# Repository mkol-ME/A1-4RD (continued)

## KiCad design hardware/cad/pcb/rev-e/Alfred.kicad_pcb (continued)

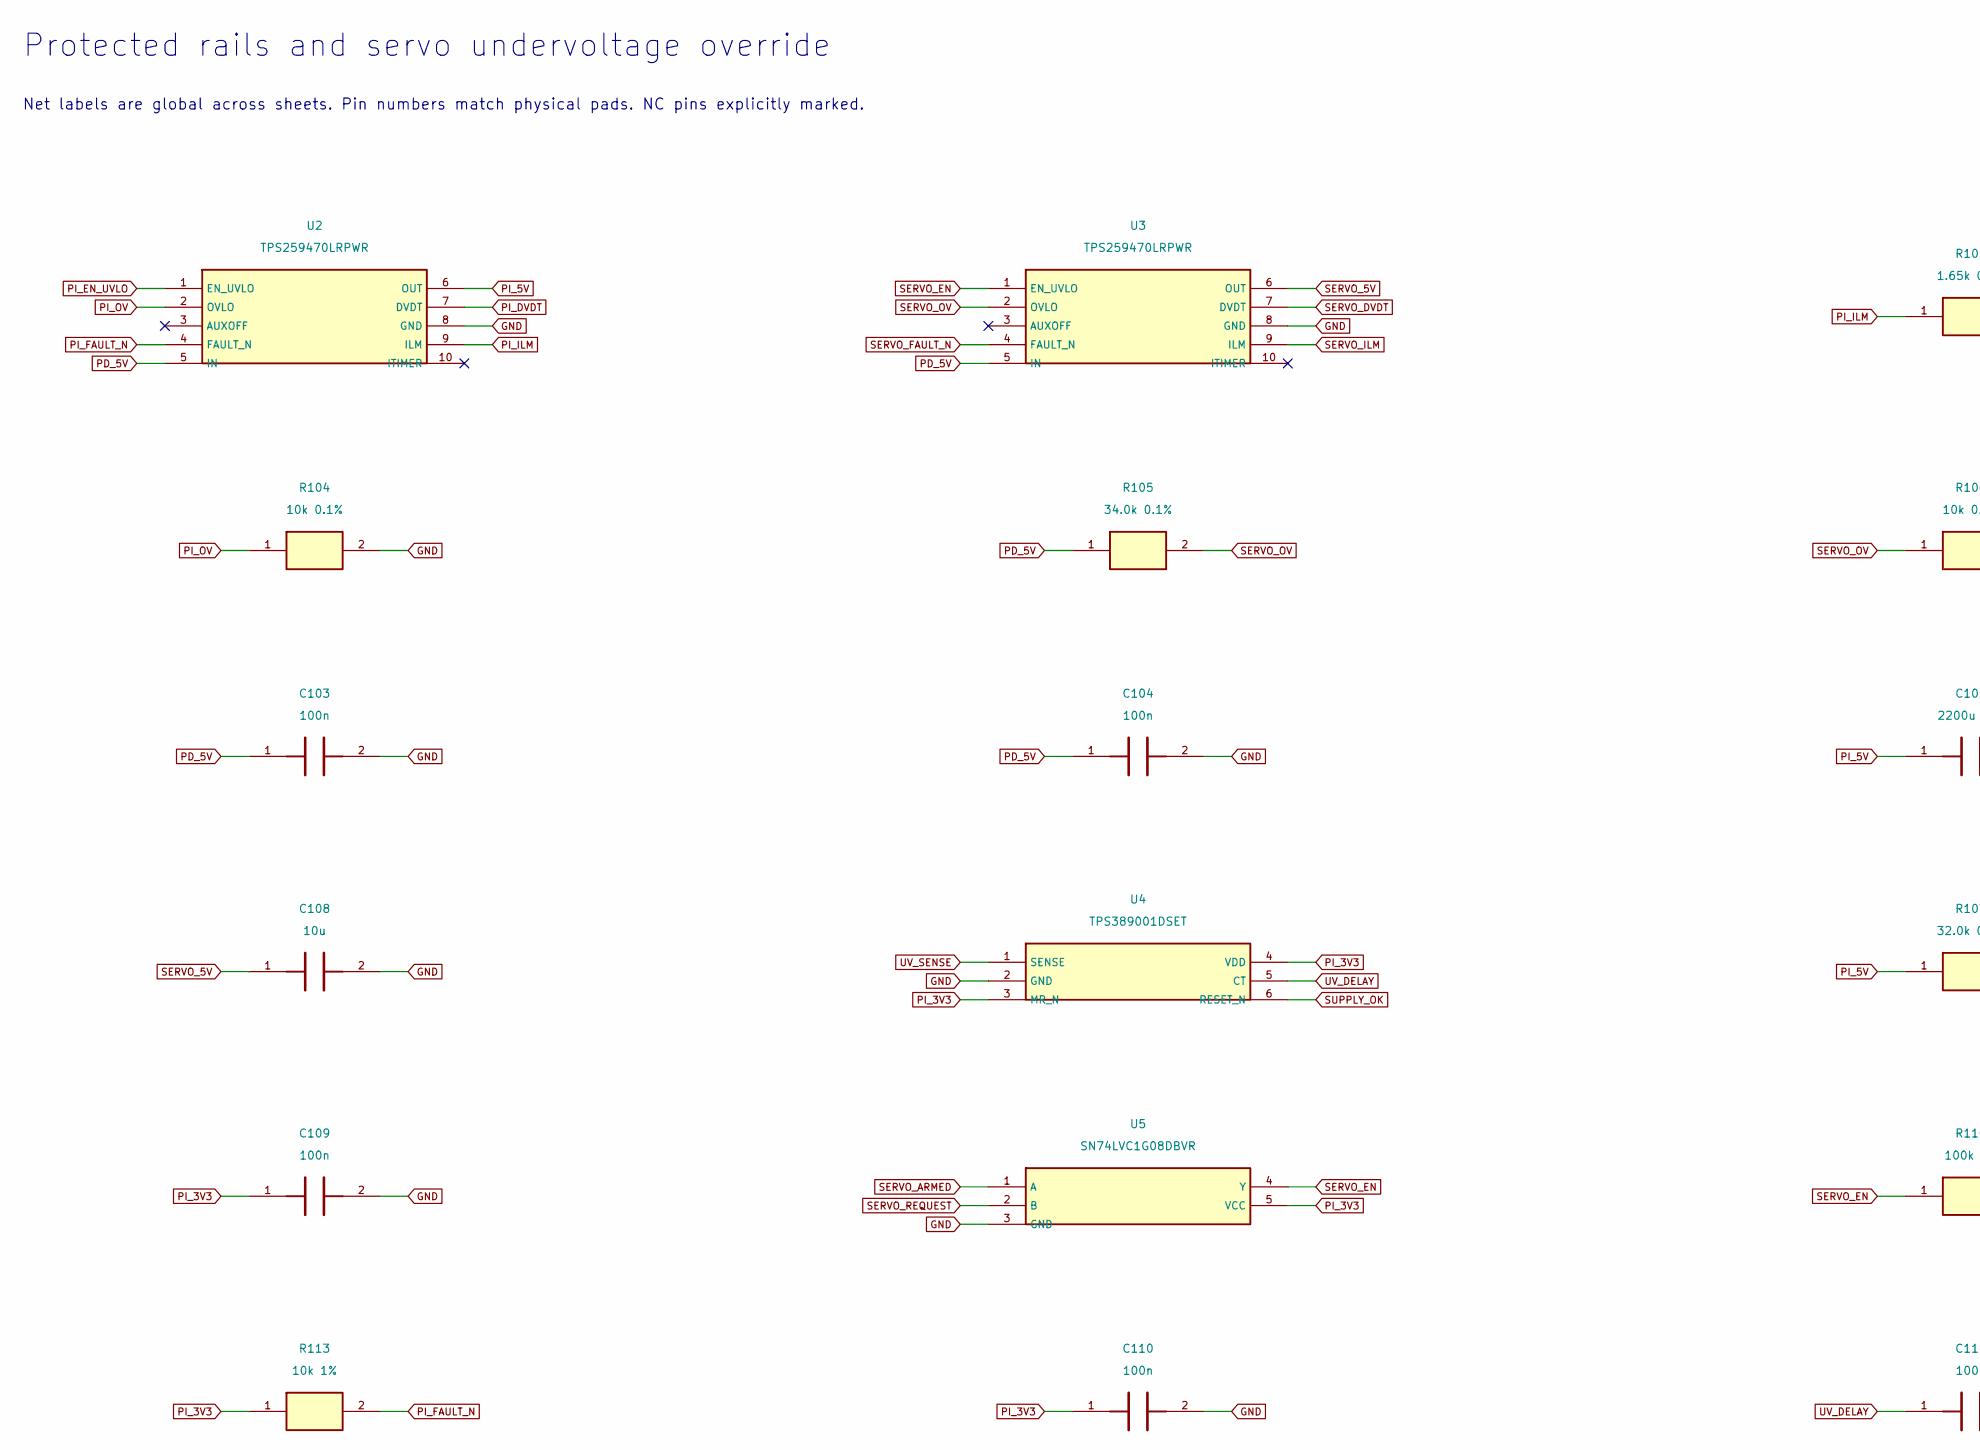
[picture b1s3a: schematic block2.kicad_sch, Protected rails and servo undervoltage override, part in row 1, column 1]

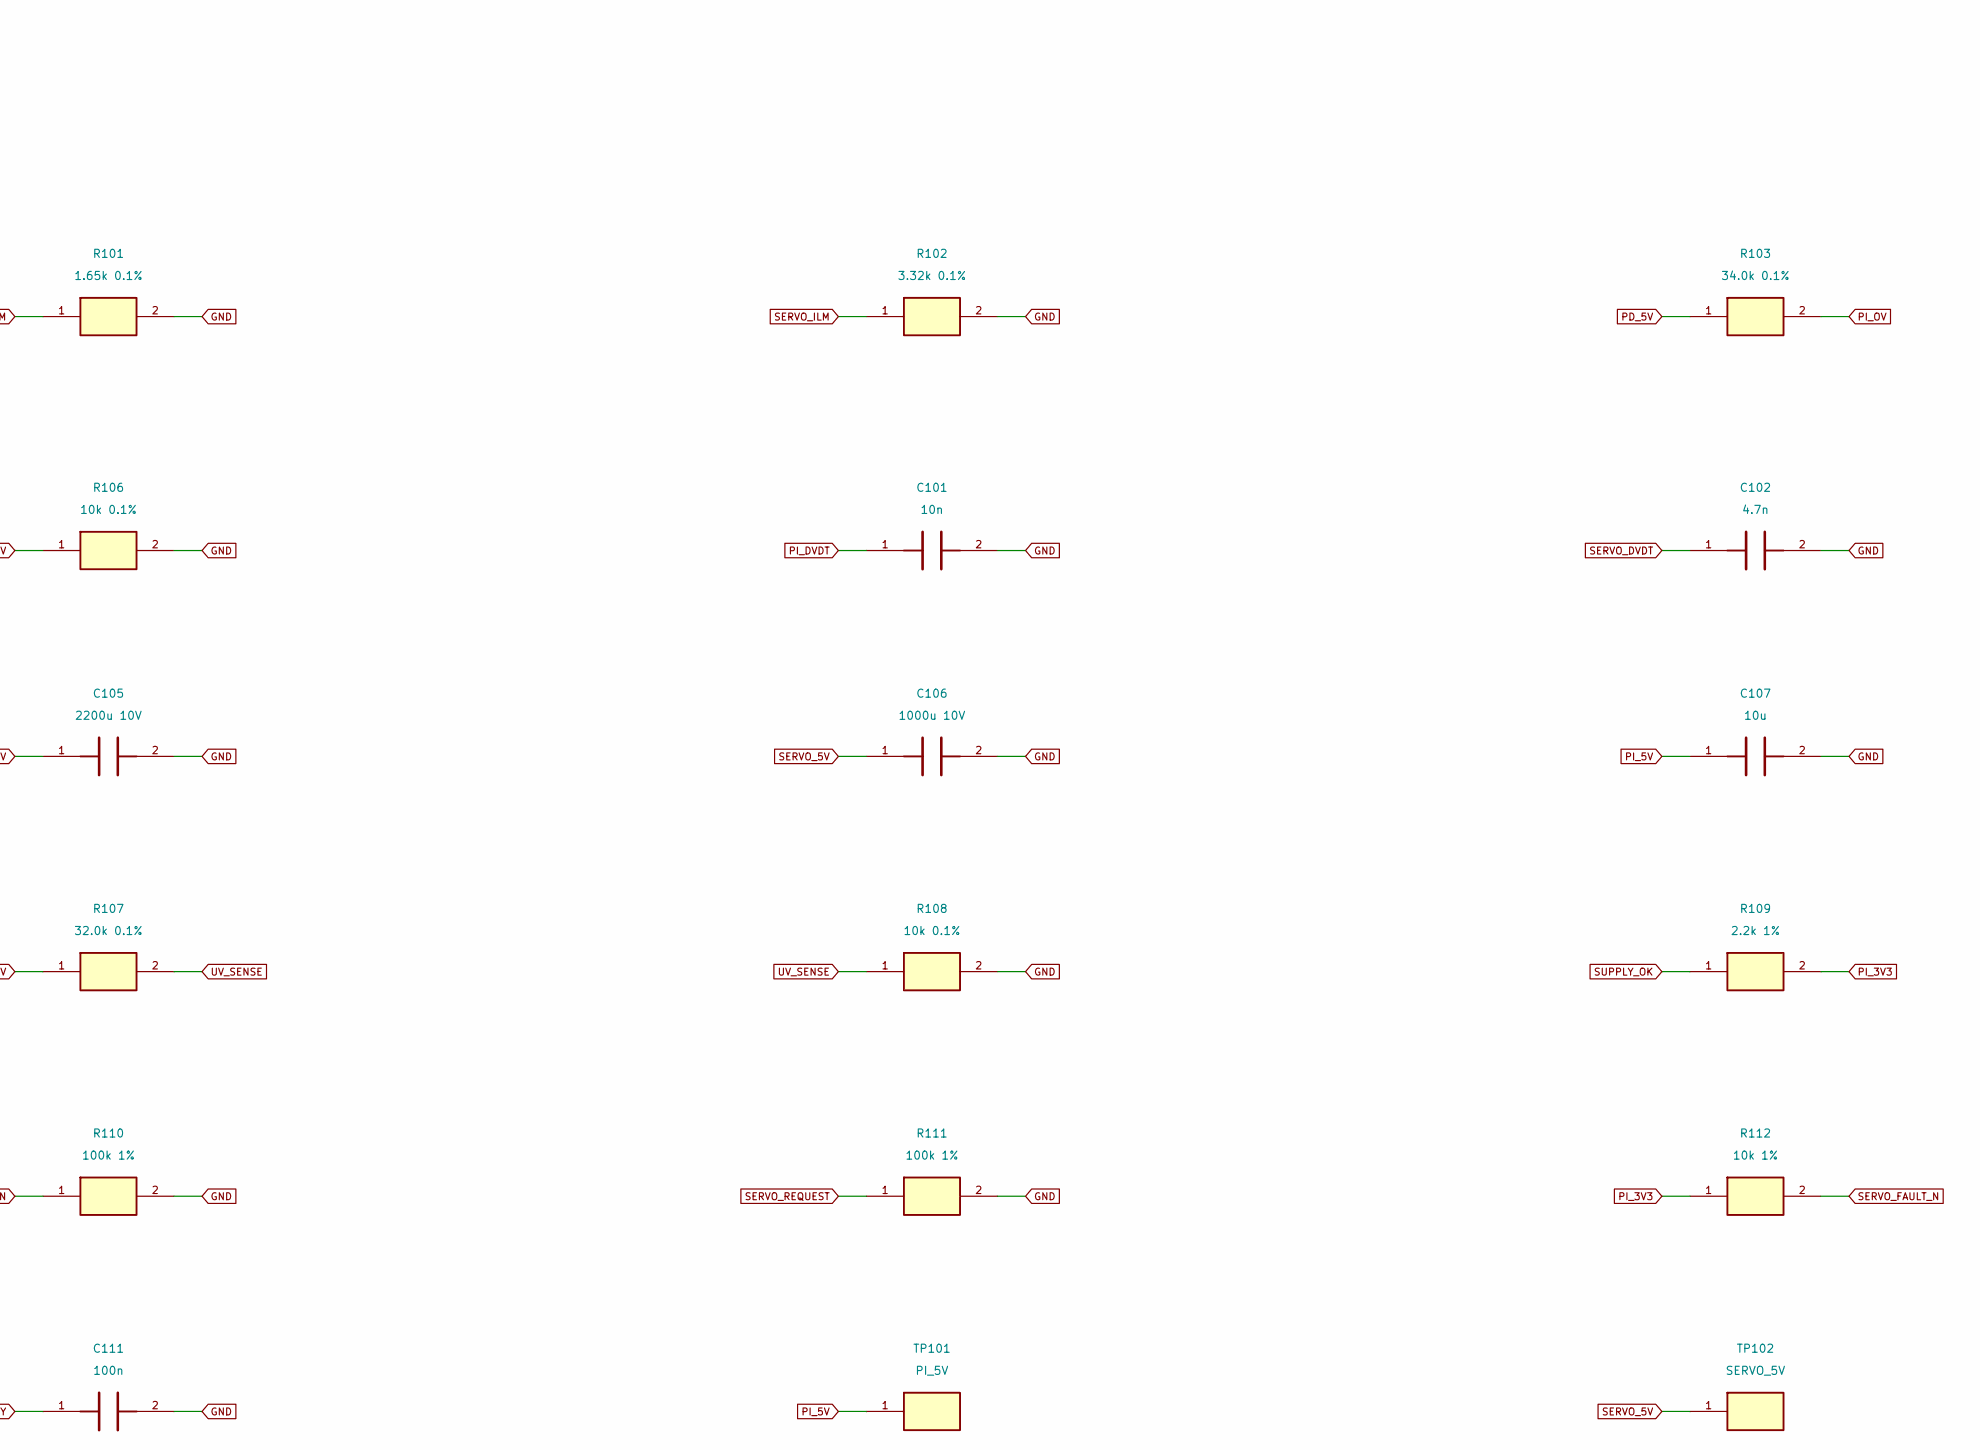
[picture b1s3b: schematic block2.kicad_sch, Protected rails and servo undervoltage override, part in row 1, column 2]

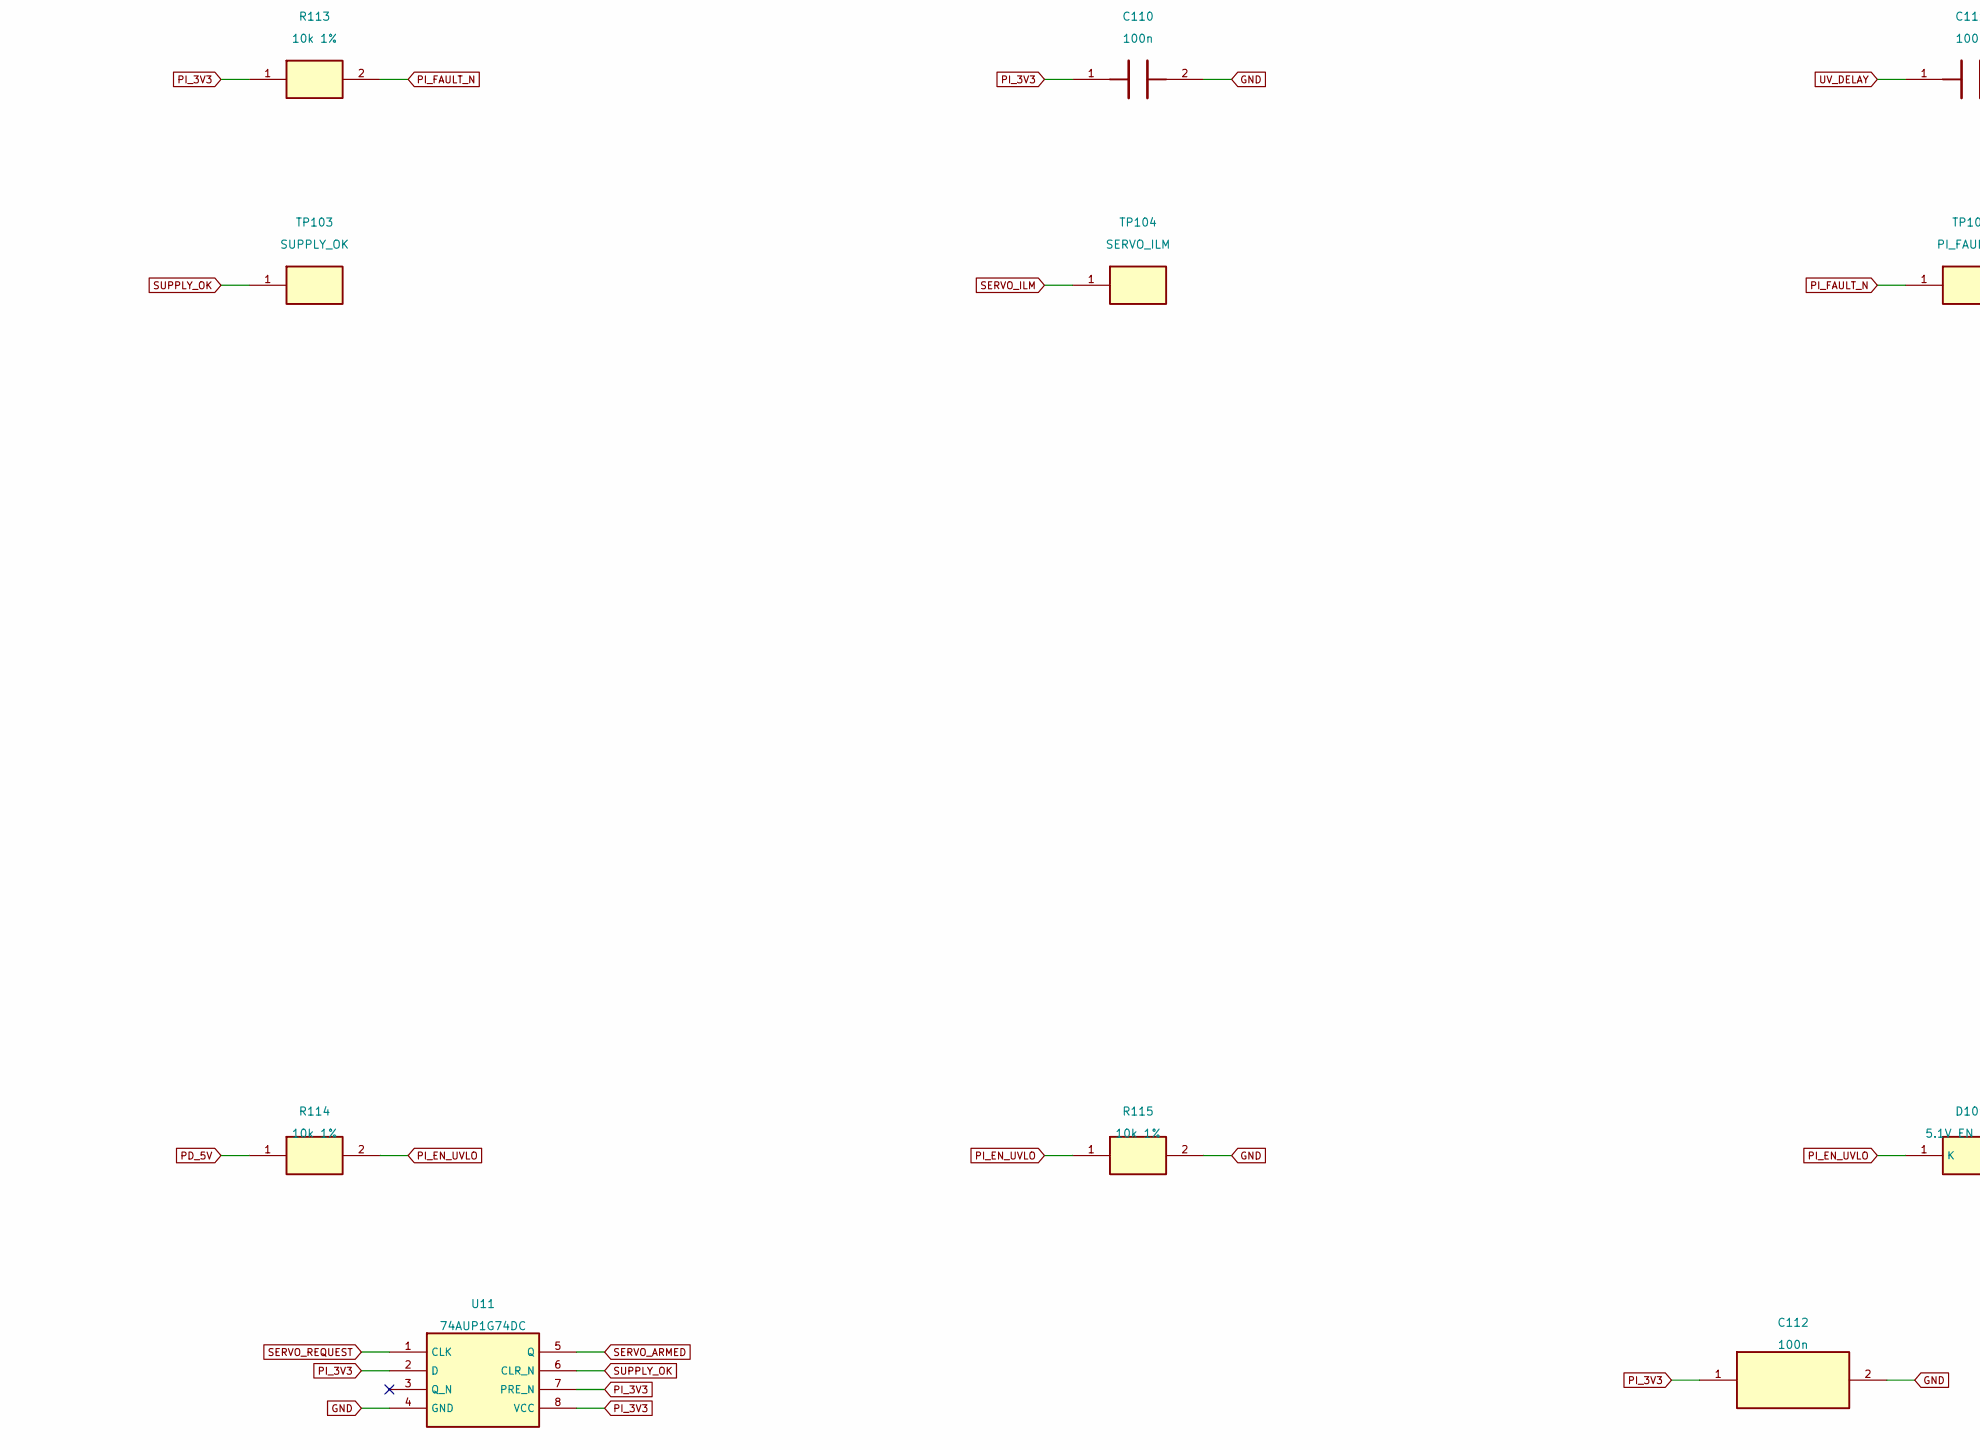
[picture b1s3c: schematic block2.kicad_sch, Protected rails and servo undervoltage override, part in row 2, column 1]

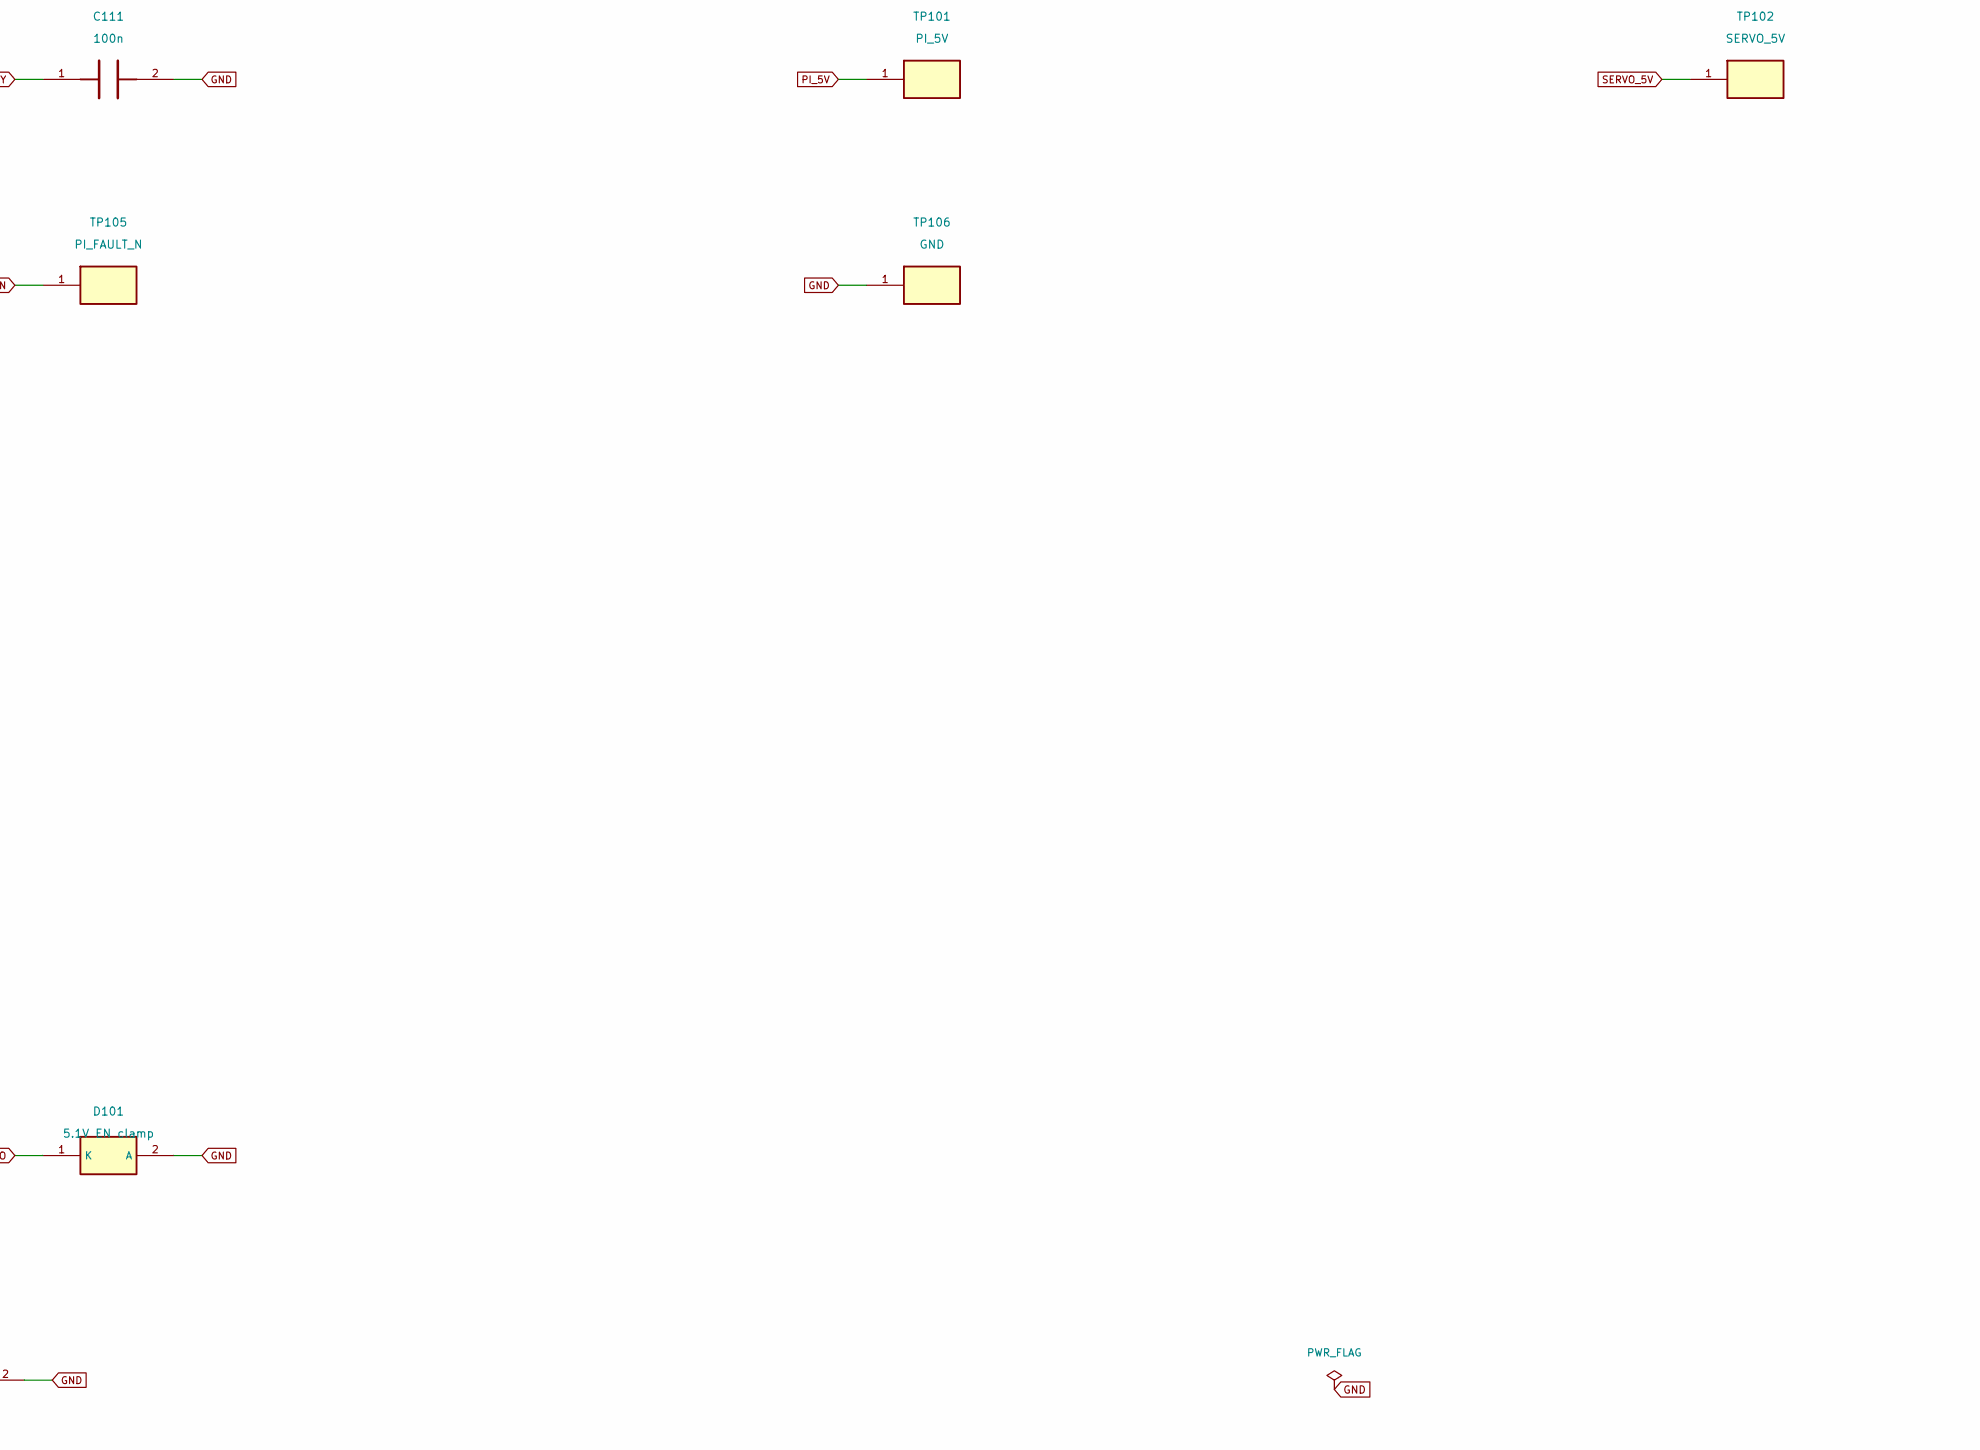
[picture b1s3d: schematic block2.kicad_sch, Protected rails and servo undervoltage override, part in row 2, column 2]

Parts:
C101: 10n; C_0805_2012Metric; MPN C0805C103J5GACTU
C102: 4.7n; C_0805_2012Metric; MPN C0805C472J5GACTU
C103, C104, C109, C110, C111, C112: 100n; C_0805_2012Metric; MPN C0805C104K5RACTU
C105: 2200u 10V; CP_Radial_D10.0mm_P5.00mm; MPN EEU-FR1A222L
C106: 1000u 10V; CP_Radial_D8.0mm_P3.50mm; MPN EEU-FR1A102L
C107, C108: 10u; C_1206_3216Metric; MPN C1206C106K4RACTU
D101: 5.1V EN clamp; D_SOD-123; MPN MMSZ5V1T1G
R101: 1.65k 0.1%; R_0805_2012Metric; MPN RT0805BRD071K65L
R102: 3.32k 0.1%; R_0805_2012Metric; MPN RT0805BRD073K32L
R103, R105: 34.0k 0.1%; R_0805_2012Metric; MPN RT0805BRD0734KL
R104, R106, R108: 10k 0.1%; R_0805_2012Metric; MPN RT0805BRD0710KL
R107: 32.0k 0.1%; R_0805_2012Metric; MPN RT0805BRD0732KL
R109: 2.2k 1%; R_0805_2012Metric; MPN RC0805FR-072K2L
R110, R111: 100k 1%; R_0805_2012Metric; MPN RC0805FR-07100KL
R112, R113, R114, R115: 10k 1%; R_0805_2012Metric; MPN RC0805FR-0710KL
TP101: PI_5V; TestPoint_Pad_D1.5mm; MPN PCB copper test point
TP102: SERVO_5V; TestPoint_Pad_D1.5mm; MPN PCB copper test point
TP103: SUPPLY_OK; TestPoint_Pad_D1.5mm; MPN PCB copper test point
TP104: SERVO_ILM; TestPoint_Pad_D1.5mm; MPN PCB copper test point
TP105: PI_FAULT_N; TestPoint_Pad_D1.5mm; MPN PCB copper test point
TP106: GND; TestPoint_Pad_D1.5mm; MPN PCB copper test point
U2, U3: TPS259470LRPWR; TI_RPW0010A; MPN TPS259470LRPWR
U4: TPS389001DSET; WSON-6_1.5x1.5mm_P0.5mm; MPN TPS389001DSET
U5: SN74LVC1G08DBVR; SOT-23-5; MPN SN74LVC1G08DBVR
U11: 74AUP1G74DC; VSSOP-8_2.3x2mm_P0.5mm; MPN 74AUP1G74DC,125

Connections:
GND: C101.2, C102.2, C103.2, C104.2, C105.2, C106.2, C107.2, C108.2, C109.2, C110.2, C111.2, C112.2, D101.2 (A), R101.2, R102.2, R104.2, R106.2, R108.2, R110.2, R111.2, R115.2, TP106.1, U2.8 (GND), U3.8 (GND), U4.2 (GND), U5.3 (GND), U11.4 (GND); also elsewhere on the board
PD_5V: C103.1, C104.1, R103.1, R105.1, R114.1, U2.5 (IN), U3.5 (IN); also elsewhere on the board
PI_3V3: C109.1, C110.1, C112.1, R109.2, R112.1, R113.1, U4.3 (MR_N), U4.4 (VDD), U5.5 (VCC), U11.2 (D), U11.7 (PRE_N), U11.8 (VCC); also elsewhere on the board
PI_5V: C105.1, C107.1, R107.1, TP101.1, U2.6 (OUT); also elsewhere on the board
PI_DVDT: C101.1, U2.7 (DVDT)
PI_EN_UVLO: D101.1 (K), R114.2, R115.1, U2.1 (EN_UVLO)
PI_FAULT_N: R113.2, TP105.1, U2.4 (FAULT_N)
PI_ILM: R101.1, U2.9 (ILM)
PI_OV: R103.2, R104.1, U2.2 (OVLO)
SERVO_5V: C106.1, C108.1, TP102.1, U3.6 (OUT); also elsewhere on the board
SERVO_ARMED: U5.1 (A), U11.5 (Q)
SERVO_DVDT: C102.1, U3.7 (DVDT)
SERVO_EN: R110.1, U3.1 (EN_UVLO), U5.4 (Y); also elsewhere on the board
SERVO_FAULT_N: R112.2, U3.4 (FAULT_N); also elsewhere on the board
SERVO_ILM: R102.1, TP104.1, U3.9 (ILM)
SERVO_OV: R105.2, R106.1, U3.2 (OVLO)
SERVO_REQUEST: R111.1, U5.2 (B), U11.1 (CLK); also elsewhere on the board
SUPPLY_OK: R109.1, TP103.1, U4.6 (RESET_N), U11.6 (CLR_N); also elsewhere on the board
UV_DELAY: C111.1, U4.5 (CT)
UV_SENSE: R107.2, R108.1, U4.1 (SENSE)

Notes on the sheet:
Protected rails and servo undervoltage override
Net labels are global across sheets. Pin numbers match physical pads. NC pins explicitly marked.

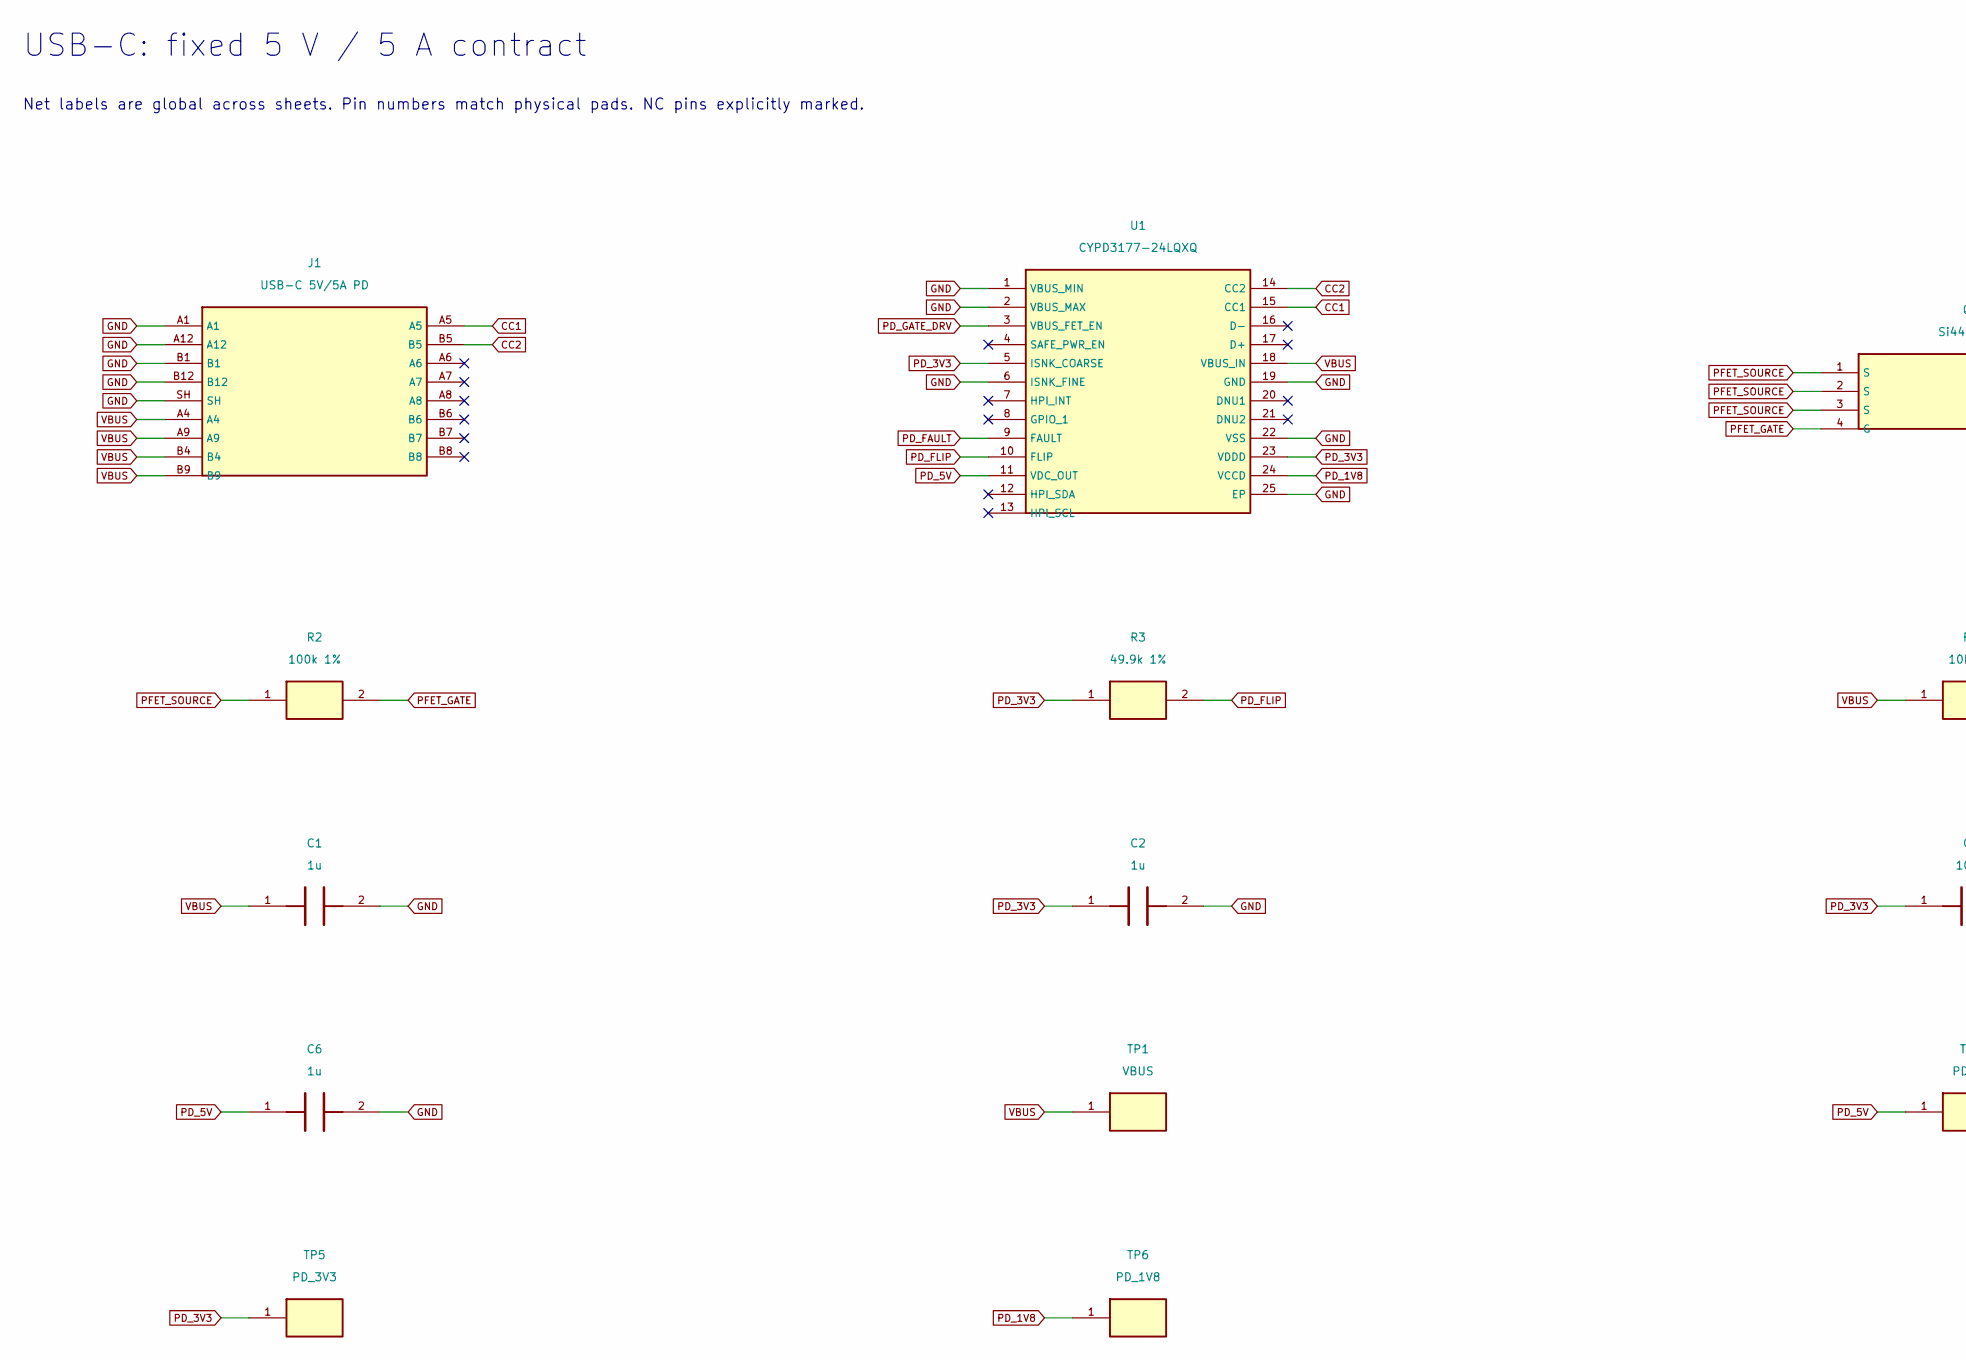
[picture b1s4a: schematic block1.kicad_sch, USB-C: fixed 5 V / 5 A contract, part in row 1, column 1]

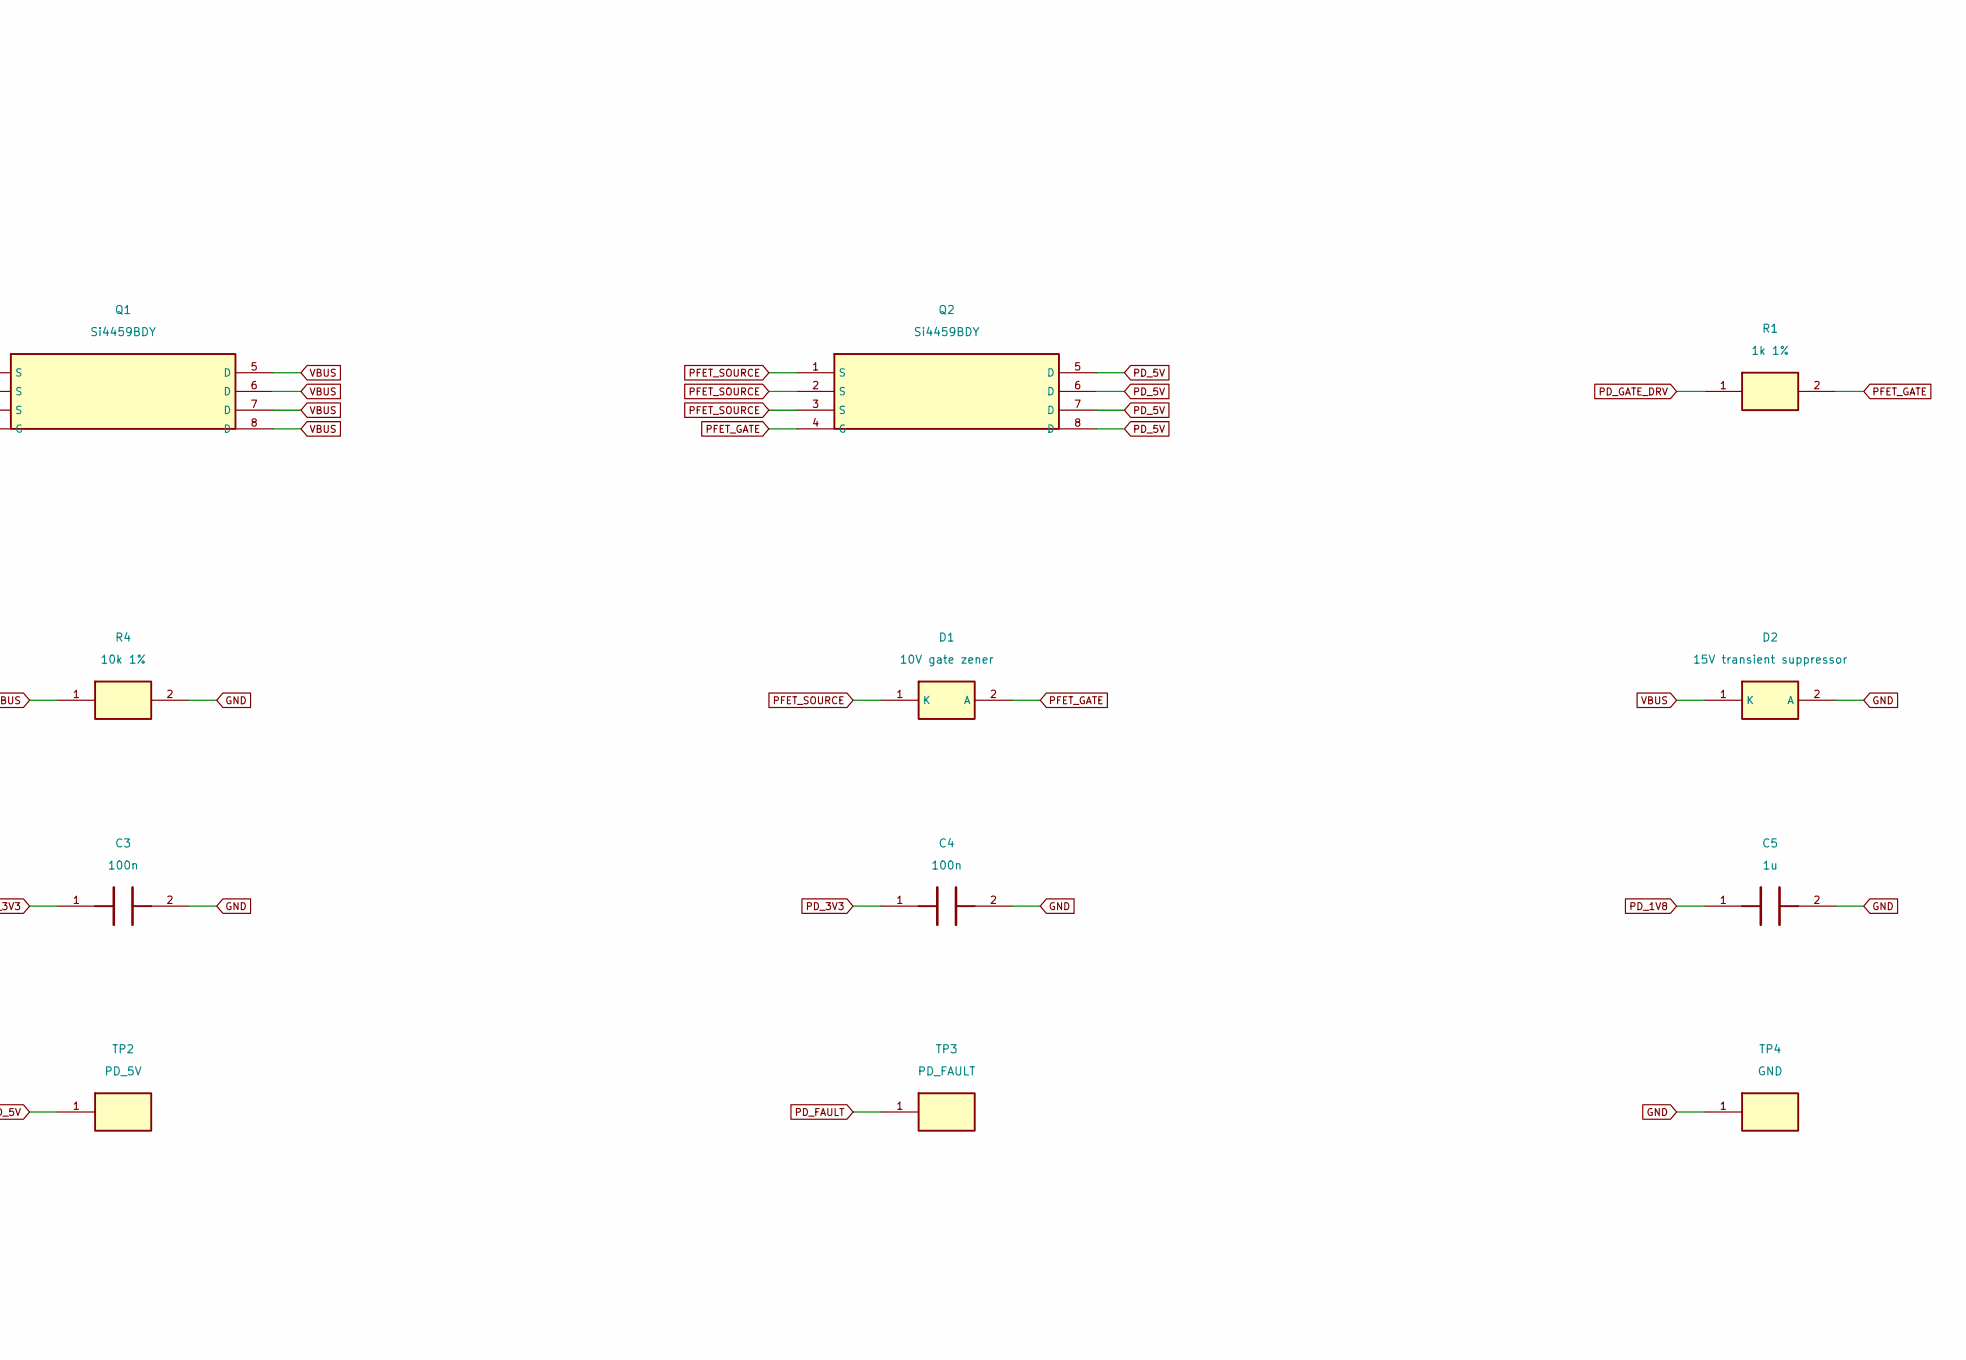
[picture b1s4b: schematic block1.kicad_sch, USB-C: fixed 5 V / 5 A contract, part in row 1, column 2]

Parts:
C1, C2, C5, C6: 1u; C_0805_2012Metric; MPN C0805C105K5RACTU
C3, C4: 100n; C_0805_2012Metric; MPN C0805C104K5RACTU
D1: 10V gate zener; D_SOD-123; MPN BZT52C10-7-F
D2: 15V transient suppressor; D_SMA; MPN SMAJ15A-13-F
J1: USB-C 5V/5A PD; USB_C_Receptacle_GCT_USB4105-xx-A_16P_TopMnt_Horizontal; MPN USB4105-GF-A
Q1, Q2: Si4459BDY; SO-8_3.9x4.9mm_P1.27mm; MPN SI4459BDY-T1-GE3
R1: 1k 1%; R_0805_2012Metric; MPN RC0805FR-071KL
R2: 100k 1%; R_0805_2012Metric; MPN RC0805FR-07100KL
R3: 49.9k 1%; R_0805_2012Metric; MPN RC0805FR-0749K9L
R4: 10k 1%; R_0805_2012Metric; MPN RC0805FR-0710KL
TP1: VBUS; TestPoint_Pad_D1.5mm; MPN PCB copper test point
TP2: PD_5V; TestPoint_Pad_D1.5mm; MPN PCB copper test point
TP3: PD_FAULT; TestPoint_Pad_D1.5mm; MPN PCB copper test point
TP4: GND; TestPoint_Pad_D1.5mm; MPN PCB copper test point
TP5: PD_3V3; TestPoint_Pad_D1.5mm; MPN PCB copper test point
TP6: PD_1V8; TestPoint_Pad_D1.5mm; MPN PCB copper test point
U1: CYPD3177-24LQXQ; QFN-24-1EP_4x4mm_P0.5mm_EP2.75x2.75mm; MPN CYPD3177-24LQXQ

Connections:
CC1: J1.A5, U1.15 (CC1)
CC2: J1.B5, U1.14 (CC2)
GND: C1.2, C2.2, C3.2, C4.2, C5.2, C6.2, D2.2 (A), J1.A1, J1.A12, J1.B1, J1.B12, J1.SH, R4.2, TP4.1, U1.1 (VBUS_MIN), U1.2 (VBUS_MAX), U1.6 (ISNK_FINE), U1.19 (GND), U1.22 (VSS), U1.25 (EP); also elsewhere on the board
PD_1V8: C5.1, TP6.1, U1.24 (VCCD)
PD_3V3: C2.1, C3.1, C4.1, R3.1, TP5.1, U1.5 (ISNK_COARSE), U1.23 (VDDD)
PD_5V: C6.1, Q2.5 (D), Q2.6 (D), Q2.7 (D), Q2.8 (D), TP2.1, U1.11 (VDC_OUT); also elsewhere on the board
PD_FAULT: TP3.1, U1.9 (FAULT)
PD_FLIP: R3.2, U1.10 (FLIP)
PD_GATE_DRV: R1.1, U1.3 (VBUS_FET_EN)
PFET_GATE: D1.2 (A), Q1.4 (G), Q2.4 (G), R1.2, R2.2
PFET_SOURCE: D1.1 (K), Q1.1 (S), Q1.2 (S), Q1.3 (S), Q2.1 (S), Q2.2 (S), Q2.3 (S), R2.1
VBUS: C1.1, D2.1 (K), J1.A4, J1.A9, J1.B4, J1.B9, Q1.5 (D), Q1.6 (D), Q1.7 (D), Q1.8 (D), R4.1, TP1.1, U1.18 (VBUS_IN)

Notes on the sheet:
Net labels are global across sheets. Pin numbers match physical pads. NC pins explicitly marked.
USB-C: fixed 5 V / 5 A contract
